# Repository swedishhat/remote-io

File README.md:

# Remote-IO (a.k.a. Pi-Dock )
_A Raspberry Pi breakout board for monitoring boat electronics_

**Patrick Lloyd in cahoots with Mirage Manufacturing**

##  Overview

### Power
* Input: 12V deep cycle marine battery (so somewhere between 10V to 13V). Regulate to 5V for back-powering the Pi through custom HAT
* 3V3 for peripherals is taken care of by Pi's on-board LDO
* Regulator: 3A buck regulator. Pi requires 1.3A at all times but recommended to support 2A. A 3A regulator should then be sufficient. Potential choices:
  * [TI LM2596](http://www.ti.com/lit/ds/symlink/lm2596.pdf)
  * [Micrel MIC24085](http://www.micrel.com/_PDF/MIC24085.pdf)
  * [Diodes Incorporated AP1506](http://www.diodes.com/datasheets/AP1506.pdf)
* More or less and an implementation of the application example circuit in the [HAT Design Guide](https://github.com/raspberrypi/hats/blob/master/designguide.md#back-powering-the-pi-via-the-j8-gpio-header)
* Raspberry Pi suggests an [ideal safety diode](https://github.com/raspberrypi/hats/blob/master/zvd-circuit.png) to allow back-powering through the header while connected to USB

### Analog
* MCP3008 ADC using at least 4 channels
* Should measure 12 & 24 Volt batteries using voltage dividers and zener diodes for protection
* Max 1 Hz sample rate (which means bit bang SPI is totally sufficient)
* [Neat article about ADC voltage dividers with enables](https://web.archive.org/web/20150816035158/http://www.microbuilder.eu/Tutorials/Fundamentals/MeasuringBatteryVoltage.aspx) (Thanks Internet Archive!)

### Digital
* Monitor switch closures. These are going to be NO or NC switches connected to ground. Connect switches directly to GPIO and use RasPi's internal pullup resistors.
* Looking at 6-8 switch input channels. We can _very_ easily add a shift register for more pins.
* GPS that talks unidirectionally to Pi over UART. Needs an RS422 level translator.
* Isolated CAN bus transceiver
* Status LEDs

## EDA
* Schematic to be drawn in KiCad. See the HW folder for more details

## Software
* Raspbian Linux
* Do as much as possible in Python since there is not much timing-critical activity

## Mechanical Design
* RemoteIO is to be implemented as a **Raspberry Pi 2 HAT**
* All input connections are going to made with screw terminals
* It should include 4 mounting holes for #8 fasteners.
* [This guy](https://github.com/disk91/hat-design) built some B+ hat templates with built-in eeprom and [has some tutorials](http://www.disk91.com/2015/technology/hardware/design-a-raspberry-pi-hat-shield/) on how to flash it and interface with it as per the Raspi [recommended guidelines](https://github.com/raspberrypi/hats).

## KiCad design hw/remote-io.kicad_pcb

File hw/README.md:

# Pi-Dock
### Raspberry Pi breakout board for monitoring boat electronics
Patrick Lloyd, Mirage Manufacturing

### Power Section
* Input power: 12V nominal (10-13v); regulates it to 5V for the pi. Uses Pi's onboard 3V3 regulator for peripherals.
* Uses LM2596 3A buck regulator for 5V fixed output.
* More or less and an implementation of the application example circuit.

### Analog Section
* MCP3008 ADC using at least 4 channels. Microchip makes pieces-of-shit for their products
* Should measure 12 & 24 Volt batteries
* Max 1 Hz sample rate

### Digital section
* Monitor switch closures. These are going to be NO or NC switches connected to ground.
* Looking at 6-8 input channels.
* UART, an RS422 level translator should be connected to the UART-Rx to allow connection to a GPS.

### Mechanical Design
* All input connections are going to made with screw terminals
* The interface to the raspberry pi should be a 26pin ribbon cable, male headers either shrouded or un-shrouded.
* It should also include 4 mounting holes for #8 fasteners.

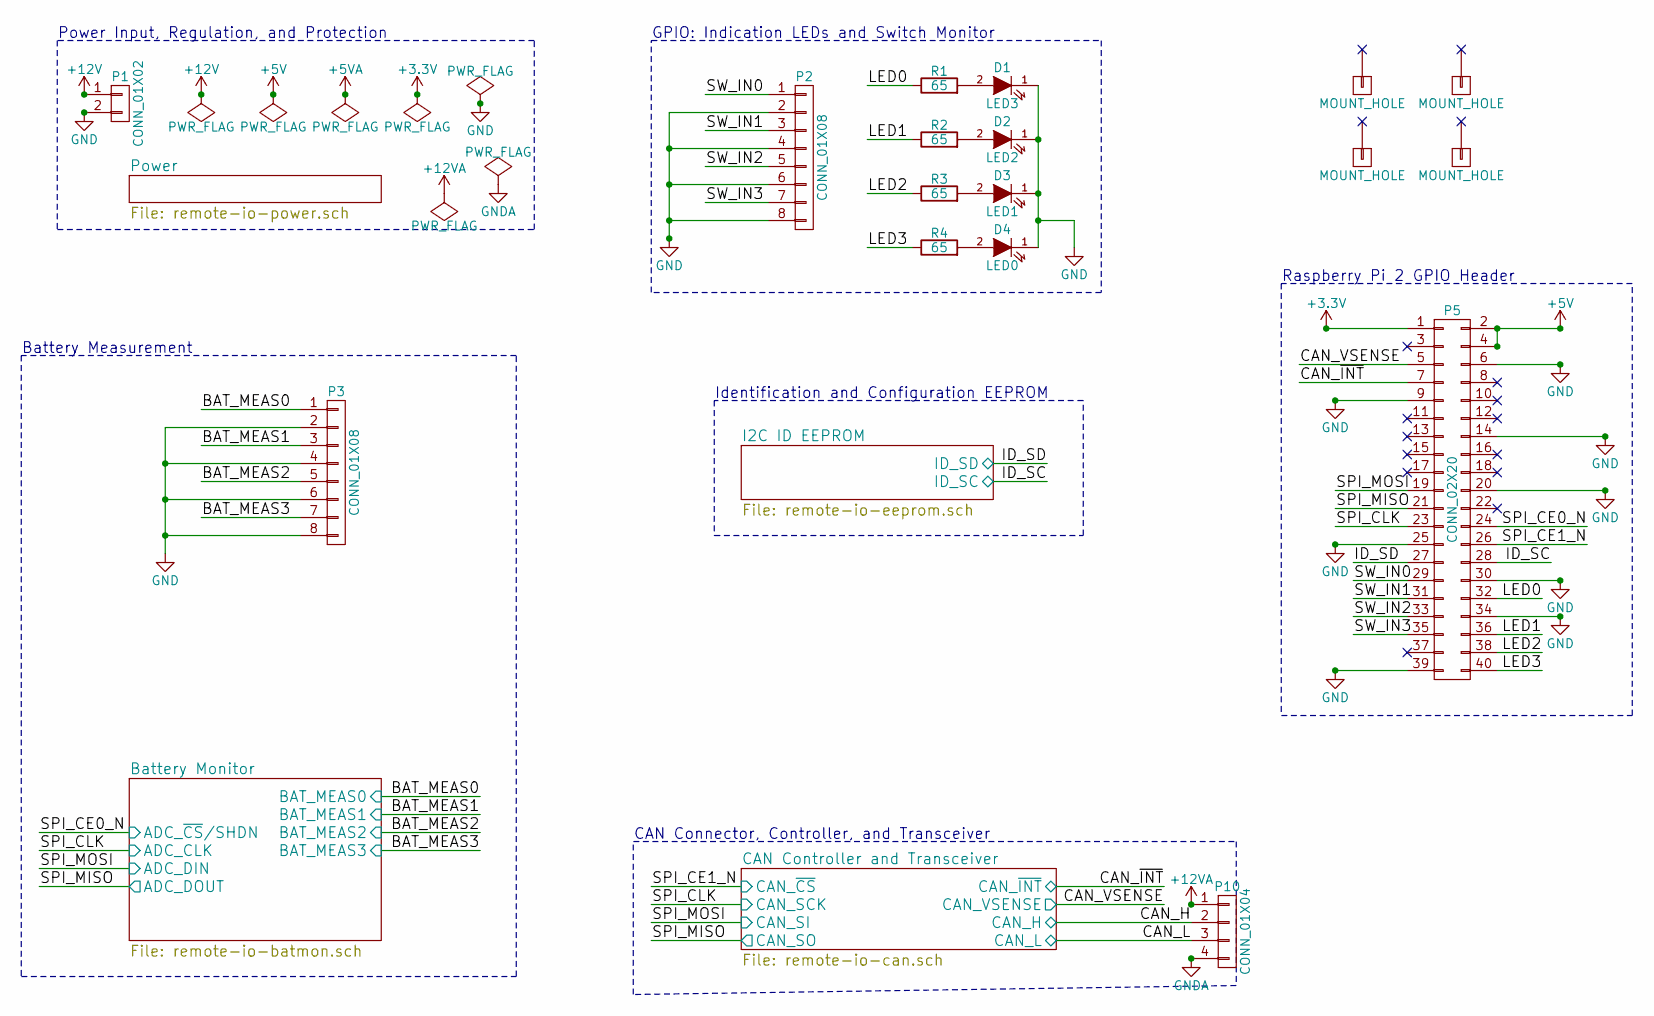
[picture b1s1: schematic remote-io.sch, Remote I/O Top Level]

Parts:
D1: LED3; LED-0805
D2: LED2; LED-0805
D3: LED1; LED-0805
D4: LED0; LED-0805
H1, H2, H3, H4: MOUNT_HOLE; MountingHole_2-7mm
P1: CONN_01X02; OSTTE020104
P2, P3: CONN_01X08; OSTTE080104
P5: CONN_02X20; Pin_Header_Straight_2x20
P10: CONN_01X04; OSTTE040104
R1, R2, R3, R4: 65; R_0805_HandSoldering

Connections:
+3V3: P5.1; also elsewhere on the board
+5V: P5.2, P5.4; also elsewhere on the board
+12V: P1.1; also elsewhere on the board
+12VA: P10.1; also elsewhere on the board
/Battery Monitor/ADC_CLK: P5.23; also elsewhere on the board
/Battery Monitor/ADC_DIN: P5.19; also elsewhere on the board
/Battery Monitor/ADC_DOUT: P5.21; also elsewhere on the board
/Battery Monitor/ADC_~CS~/SHDN: P5.24; also elsewhere on the board
/Battery Monitor/BAT_MEAS0: P3.1; also elsewhere on the board
/Battery Monitor/BAT_MEAS1: P3.3; also elsewhere on the board
/Battery Monitor/BAT_MEAS2: P3.5; also elsewhere on the board
/Battery Monitor/BAT_MEAS3: P3.7; also elsewhere on the board
/CAN Controller and Transceiver/CAN_H: P10.2; also elsewhere on the board
/CAN Controller and Transceiver/CAN_L: P10.3; also elsewhere on the board
/CAN Controller and Transceiver/CAN_VSENSE: P5.5; also elsewhere on the board
/CAN Controller and Transceiver/CAN_~CS: P5.26; also elsewhere on the board
/CAN Controller and Transceiver/CAN_~INT: P5.7; also elsewhere on the board
/I2C ID EEPROM/ID_SC: P5.28; also elsewhere on the board
/I2C ID EEPROM/ID_SD: P5.27; also elsewhere on the board
/LED0: P5.32, R1.1
/LED1: P5.36, R2.1
/LED2: P5.38, R3.1
/LED3: P5.40, R4.1
/SW_IN0: P2.1, P5.29
/SW_IN1: P2.3, P5.31
/SW_IN2: P2.5, P5.33
/SW_IN3: P2.7, P5.35
unnamed: D1.2 (A), R1.2
unnamed: D2.2 (A), R2.2
unnamed: D3.2 (A), R3.2
unnamed: D4.2 (A), R4.2

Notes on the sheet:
GPIO: Indication LEDs and Switch Monitor
Raspberry Pi 2 GPIO Header
Power Input, Regulation, and Protection
Battery Measurement
Identification and Configuration EEPROM
CAN Connector, Controller, and Transceiver

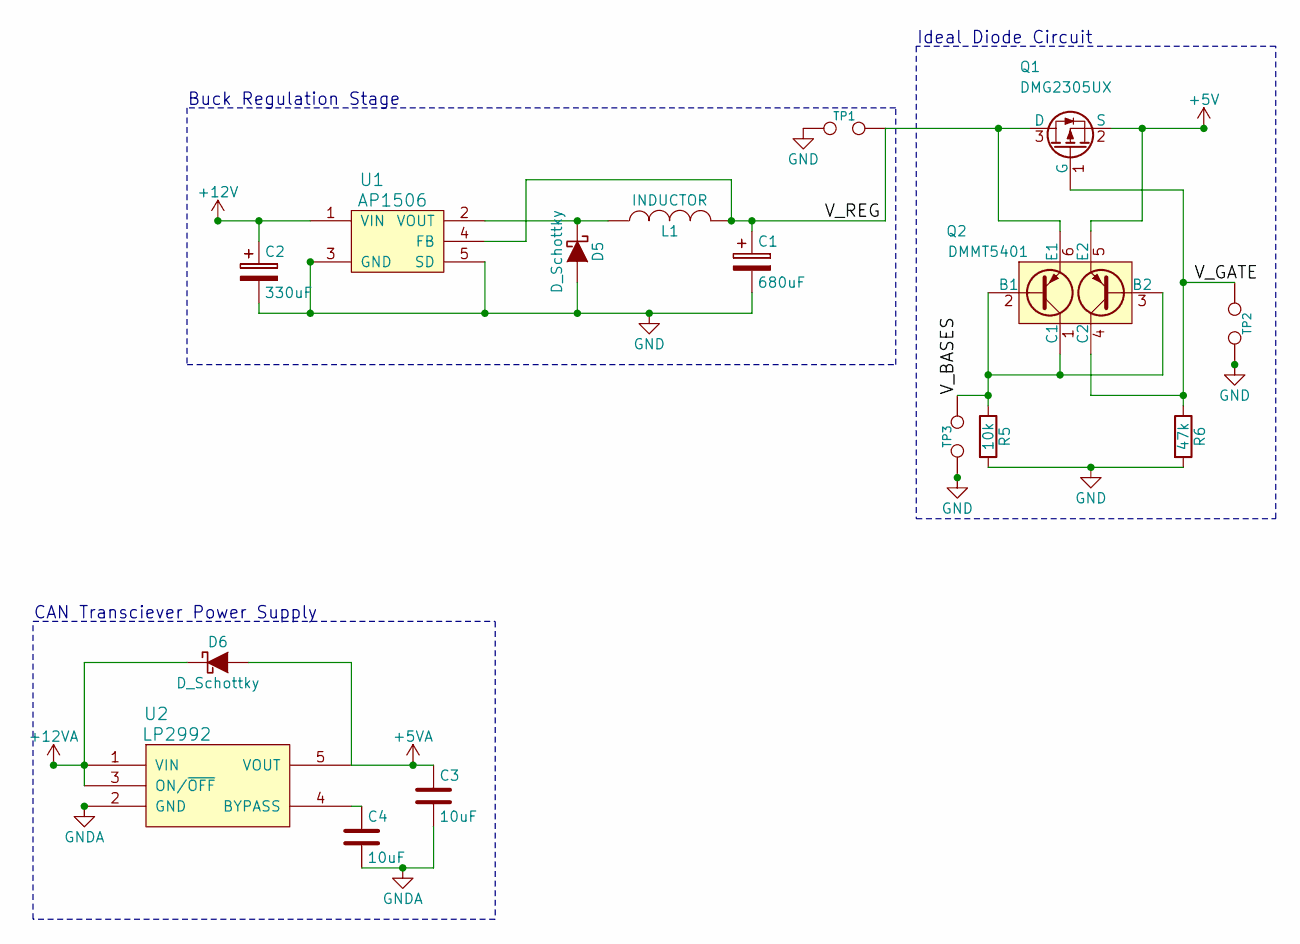
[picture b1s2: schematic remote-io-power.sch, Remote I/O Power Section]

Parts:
C1: 680uF; C_Radial_D12.5_L25_P5
C2: 330uF; C_Radial_D10_L25_P5
C3, C4: 10uF; C_0805_HandSoldering
D5, D6: D_Schottky; Diode-SMB_Handsoldering
L1: INDUCTOR; SRN1060-XXXM
Q1: DMG2305UX; SOT-23_Handsoldering
Q2: DMMT5401; SOT-23-6
R5: 10k; R_0805_HandSoldering
R6: 47k; R_0805_HandSoldering
TP1, TP2, TP3: TEST; Pin_Header_Straight_1x02
U1: AP1506; TO-263-5_HandSoldering
U2: LP2992; SOT-23-5

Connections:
+5V: Q1.2 (S), Q2.5 (E2); also elsewhere on the board
+5VA: C3.1, D6.2 (A), U2.5 (VOUT); also elsewhere on the board
+12V: C2.1, U1.1 (VIN); also elsewhere on the board
+12VA: D6.1 (K), U2.1 (VIN), U2.3 (ON/~OFF); also elsewhere on the board
/Power/V_BASES: Q2.1 (C1), Q2.2 (B1), Q2.3 (B2), R5.1, TP3.1
/Power/V_GATE: Q1.1 (G), Q2.4 (C2), R6.1, TP2.1
/Power/V_REG: C1.1, L1.2, Q1.3 (D), Q2.6 (E1), TP1.2, U1.4 (FB)
unnamed: C4.1, U2.4 (BYPASS)
unnamed: D5.1 (K), L1.1, U1.2 (VOUT)

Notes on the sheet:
Buck Regulation Stage
Ideal Diode Circuit
CAN Transciever Power Supply

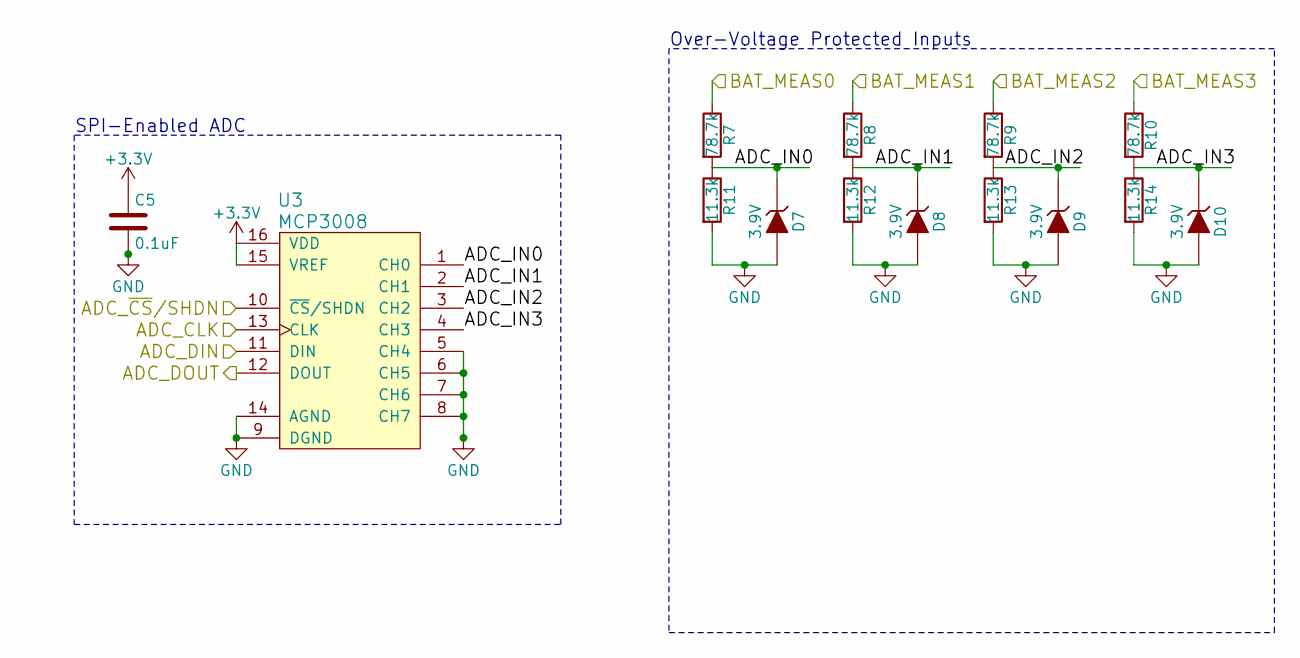
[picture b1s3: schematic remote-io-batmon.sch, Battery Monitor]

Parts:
C5: 0.1uF; C_0805_HandSoldering
D7, D8, D9, D10: 3.9V; SOD-323
R7, R8, R9, R10: 78.7k; R_0805_HandSoldering
R11, R12, R13, R14: 11.3k; R_0805_HandSoldering
U3: MCP3008; SOIC-16_3.9x9.9mm_Pitch1.27mm

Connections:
+3V3: C5.1, U3.15 (VREF), U3.16 (VDD); also elsewhere on the board
/Battery Monitor/ADC_CLK: U3.13 (CLK); also elsewhere on the board
/Battery Monitor/ADC_DIN: U3.11 (DIN); also elsewhere on the board
/Battery Monitor/ADC_DOUT: U3.12 (DOUT); also elsewhere on the board
/Battery Monitor/ADC_IN0: D7.1 (K), R7.2, R11.1, U3.1 (CH0)
/Battery Monitor/ADC_IN1: D8.1 (K), R8.2, R12.1, U3.2 (CH1)
/Battery Monitor/ADC_IN2: D9.1 (K), R9.2, R13.1, U3.3 (CH2)
/Battery Monitor/ADC_IN3: D10.1 (K), R10.2, R14.1, U3.4 (CH3)
/Battery Monitor/ADC_~CS~/SHDN: U3.10 (~CS~/SHDN); also elsewhere on the board
/Battery Monitor/BAT_MEAS0: R7.1; also elsewhere on the board
/Battery Monitor/BAT_MEAS1: R8.1; also elsewhere on the board
/Battery Monitor/BAT_MEAS2: R9.1; also elsewhere on the board
/Battery Monitor/BAT_MEAS3: R10.1; also elsewhere on the board

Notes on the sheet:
SPI-Enabled ADC
Over-Voltage Protected Inputs

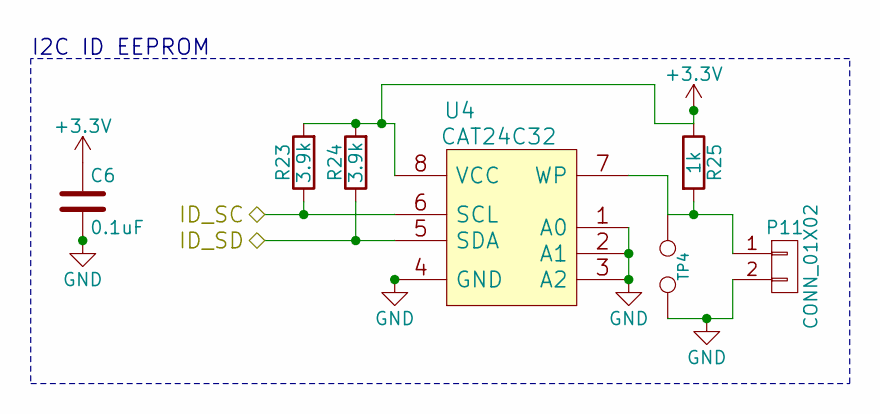
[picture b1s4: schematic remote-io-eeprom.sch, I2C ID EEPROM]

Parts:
C6: 0.1uF; C_0805_HandSoldering
P11: CONN_01X02; Pin_Header_Straight_1x02
R23, R24: 3.9k; R_0805_HandSoldering
R25: 1k; R_0805_HandSoldering
TP4: TEST; Pin_Header_Straight_1x02
U4: CAT24C32; SOIC-8_3.9x4.9mm_Pitch1.27mm

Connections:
+3V3: C6.1, R23.2, R24.2, R25.1, U4.8 (VCC); also elsewhere on the board
/I2C ID EEPROM/ID_SC: R23.1, U4.6 (SCL); also elsewhere on the board
/I2C ID EEPROM/ID_SD: R24.1, U4.5 (SDA); also elsewhere on the board
unnamed: P11.1, R25.2, TP4.1, U4.7 (WP)

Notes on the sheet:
I2C ID EEPROM

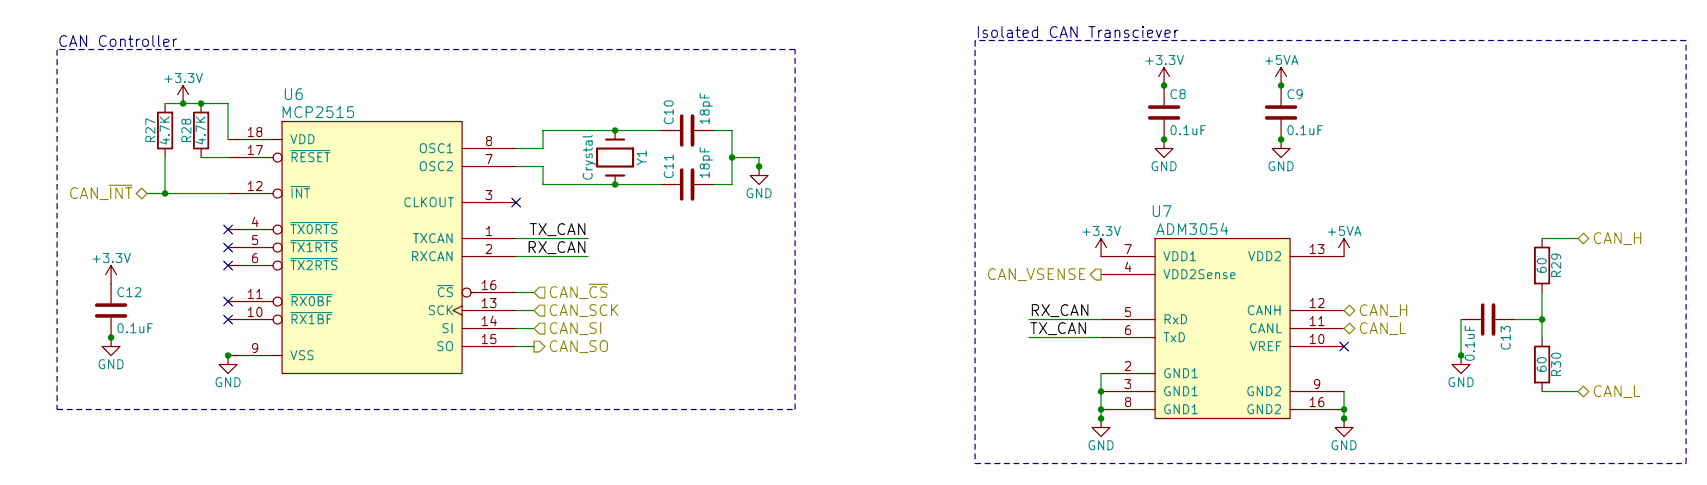
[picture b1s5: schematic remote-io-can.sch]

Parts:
C8, C9, C12, C13: 0.1uF; C_0805_HandSoldering
C10, C11: 18pF; C_0805_HandSoldering
R27, R28: 4.7K; R_0805_HandSoldering
R29, R30: 60; R_0805_HandSoldering
U6: MCP2515; SOIC-18_7.5x11.6mm_Pitch1.27mm
U7: ADM3054; SOIC-16_7.5x10.3mm_Pitch1.27mm
Y1: Crystal; Crystal_HC49-SD_SMD

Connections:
+3V3: C8.1, C12.1, R27.2, R28.2, U6.18 (VDD), U7.7 (VDD1); also elsewhere on the board
+5VA: C9.1, U7.13 (VDD2); also elsewhere on the board
/Battery Monitor/ADC_CLK: U6.13 (SCK); also elsewhere on the board
/Battery Monitor/ADC_DIN: U6.14 (SI); also elsewhere on the board
/Battery Monitor/ADC_DOUT: U6.15 (SO); also elsewhere on the board
/CAN Controller and Transceiver/CAN_H: R29.1, U7.12 (CANH); also elsewhere on the board
/CAN Controller and Transceiver/CAN_L: R30.2, U7.11 (CANL); also elsewhere on the board
/CAN Controller and Transceiver/CAN_VSENSE: U7.4 (VDD2Sense); also elsewhere on the board
/CAN Controller and Transceiver/CAN_~CS: U6.16 (~CS); also elsewhere on the board
/CAN Controller and Transceiver/CAN_~INT: R27.1, U6.12 (~INT); also elsewhere on the board
/CAN Controller and Transceiver/RX_CAN: U6.2 (RXCAN), U7.5 (RxD)
/CAN Controller and Transceiver/TX_CAN: U6.1 (TXCAN), U7.6 (TxD)
unnamed: C10.1, U6.8 (OSC1), Y1.1
unnamed: C11.1, U6.7 (OSC2), Y1.2
unnamed: C13.1, R29.2, R30.1
unnamed: R28.1, U6.17 (~RESET)

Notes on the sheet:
CAN Controller
Isolated CAN Transciever

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
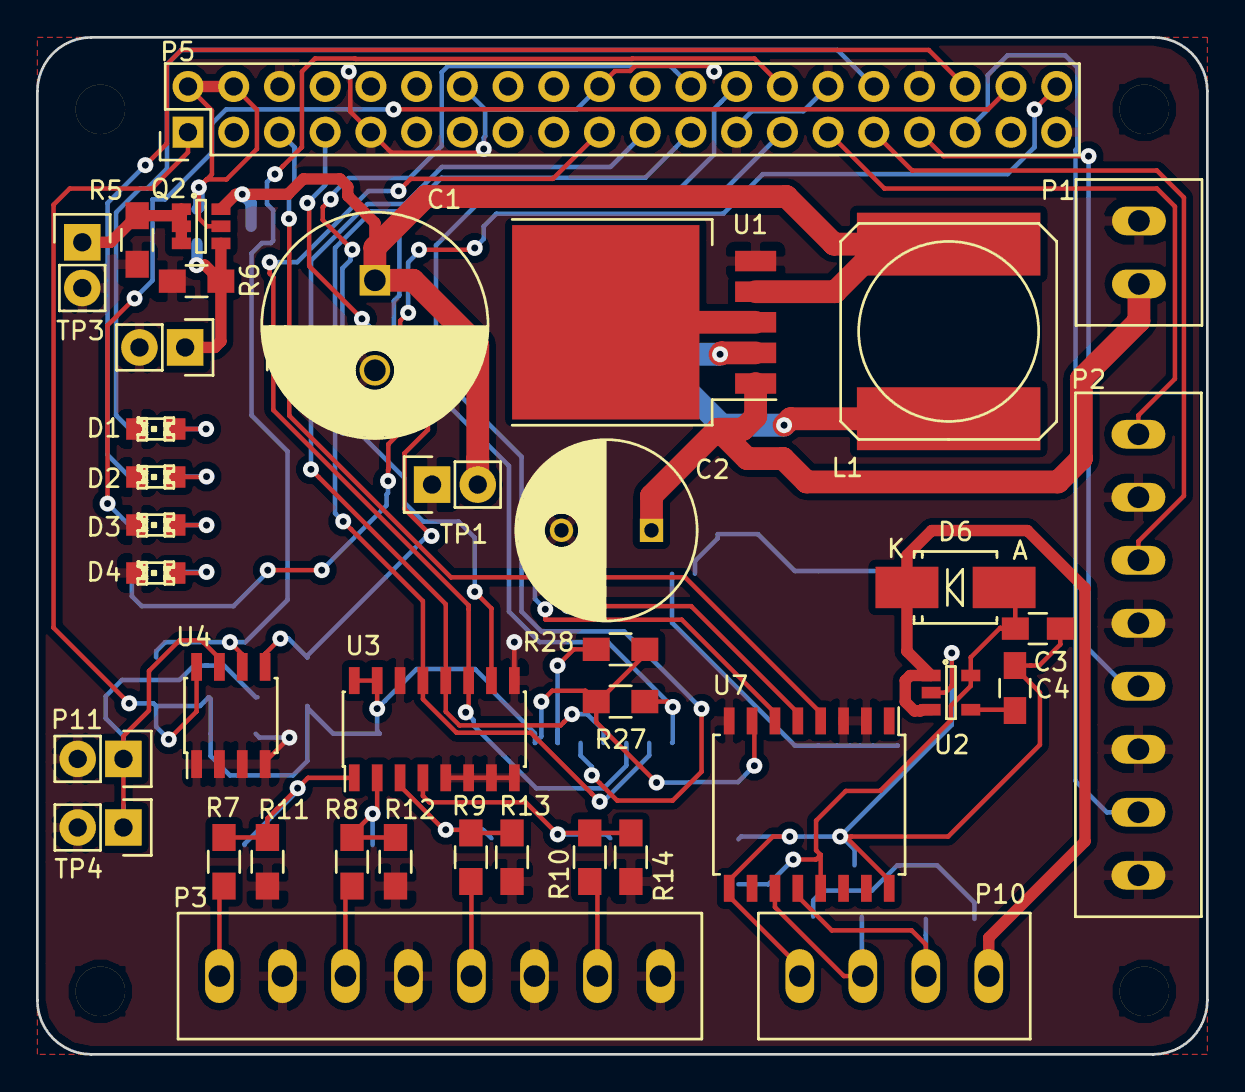
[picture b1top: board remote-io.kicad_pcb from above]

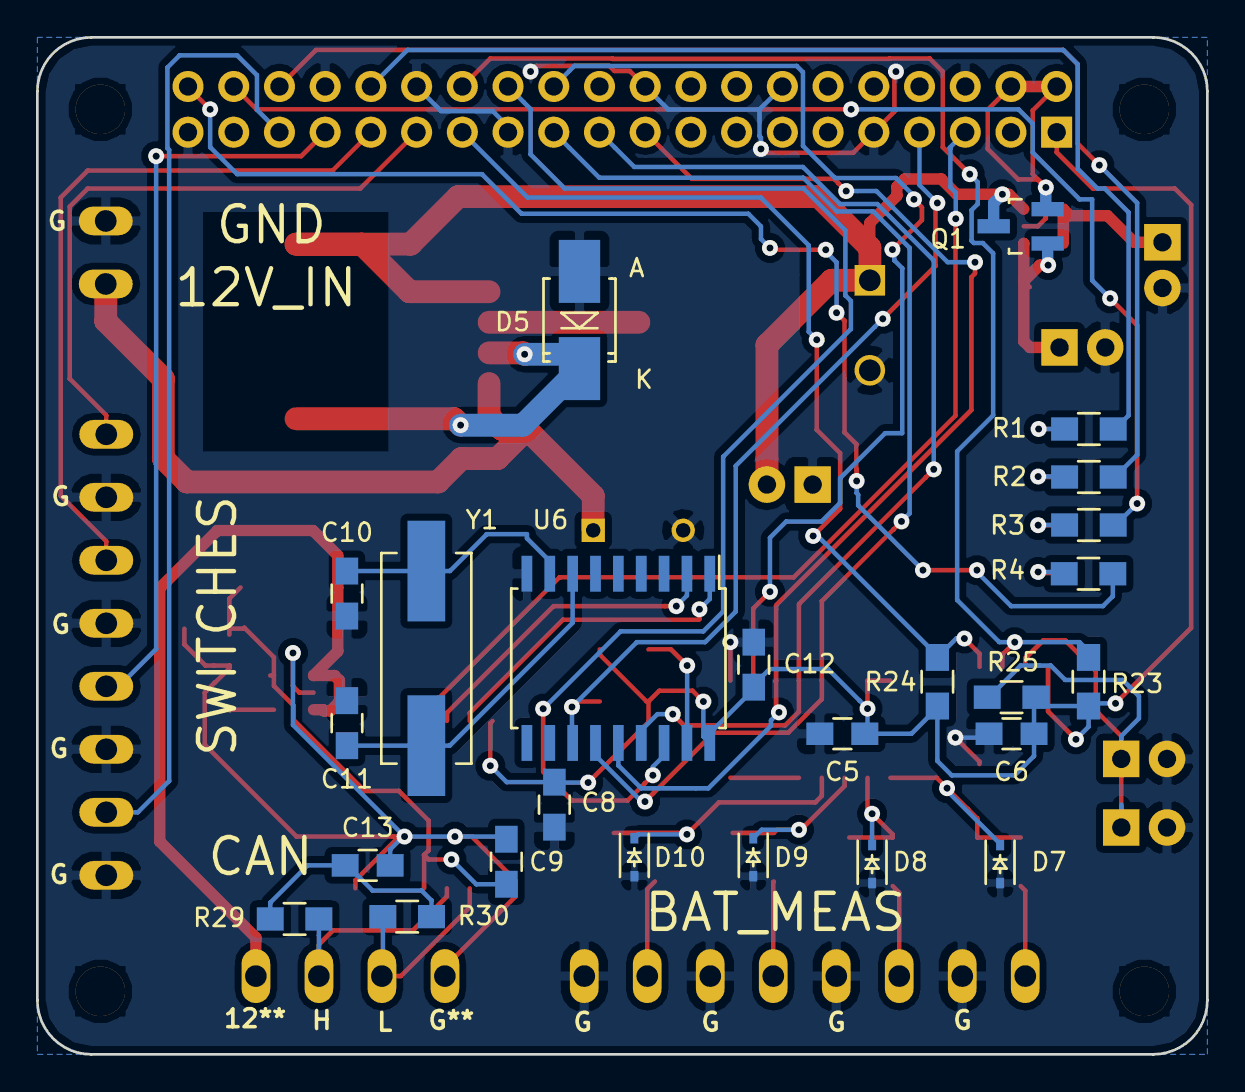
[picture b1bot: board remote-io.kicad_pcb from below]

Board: 2 copper layers, 65.0 x 56.5 mm, 67 parts (25 on the bottom side), 50 nets.

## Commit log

2015-06-15 Created readme's and directories for sw and doc
2015-06-15 Updated README file
2015-06-16 Added ADC schematic and connections
2015-06-16 Added I2C ID EEPROM
2015-06-16 Added RS-422 sheet to top level
2015-06-16 .gitignore now working
2015-06-16 Added RS-422 Receiver Circuit
2015-06-16 RS-422 Tweaks
2015-06-16 Finished first revision of schematic
2015-06-16 modified gitignore
2015-06-16 Updated .gitignore with recs from en.wikibooks.org/wiki/Kicad/file_formats
2015-06-17 Matched all footprints to schem and created kicad_pcb file
2015-06-17 added .pcb-back to gitignore and resynced
2015-06-17 Whoops. Added .kicad_pcb-back to gitignore and resynced
2015-06-17 removed autosave
2015-06-17 added CAN power, controller, and transceiver to schem and updated PCB
2015-06-17 Added reference designs
2015-06-17 Hoping to get rid of nested git repos
2015-06-17 Now I've decided to keep the nested git repos since github supports them nicely
2015-06-17 removed fucking goddamn submodules
2015-06-17 Added fucking goddamn submodules using git submodule add
2015-06-19 Started fucking aroond with pcb layout. Power is tricky...
2015-06-22 All parts in hat-spec-size board
2015-06-23 Edited board dims to get rid of flex cutout. May need to move conns to other side
2015-06-23 Preliminary routing of board. Messy but whatever... it's a rev 0
2015-06-23 removed extraneous sheets and pro files
2015-06-23 removed zones_dump.txt
2015-06-25 Isolated CAN bus connections and added proper mounting holes
2015-06-25 Finished rev 0 with gerbers and drills
2015-06-25 added invoices for BoM and tools
2015-06-29 Added PCB and schematic prints
2016-01-18 Why did I have invoices in there?
2016-01-18 Try again
2016-01-18 Updated readme and worked on SPI (outside git)
2017-03-27 Redoing it in Altium because of why not
2017-03-27 Re-added datasheets and an incorrect README
2017-03-27 Made breakout for EEPROM to test with othermill
2017-05-14 Restructure. Revving to 1, all older files considered r0_legacy
2017-05-15 Did project research. Using TI ISO1050 for can isolation and ref design in datsheet
